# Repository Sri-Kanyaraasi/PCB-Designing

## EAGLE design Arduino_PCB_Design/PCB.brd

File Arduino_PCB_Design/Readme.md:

Eagle schematic file (with the extension .sch)  
Eagle board file (with the extension .brd)  
Geerber file  
PDF for PCB (Outlayer of the PCB)  
PNG of the GERBER file (Nothing but the PCB Picture)

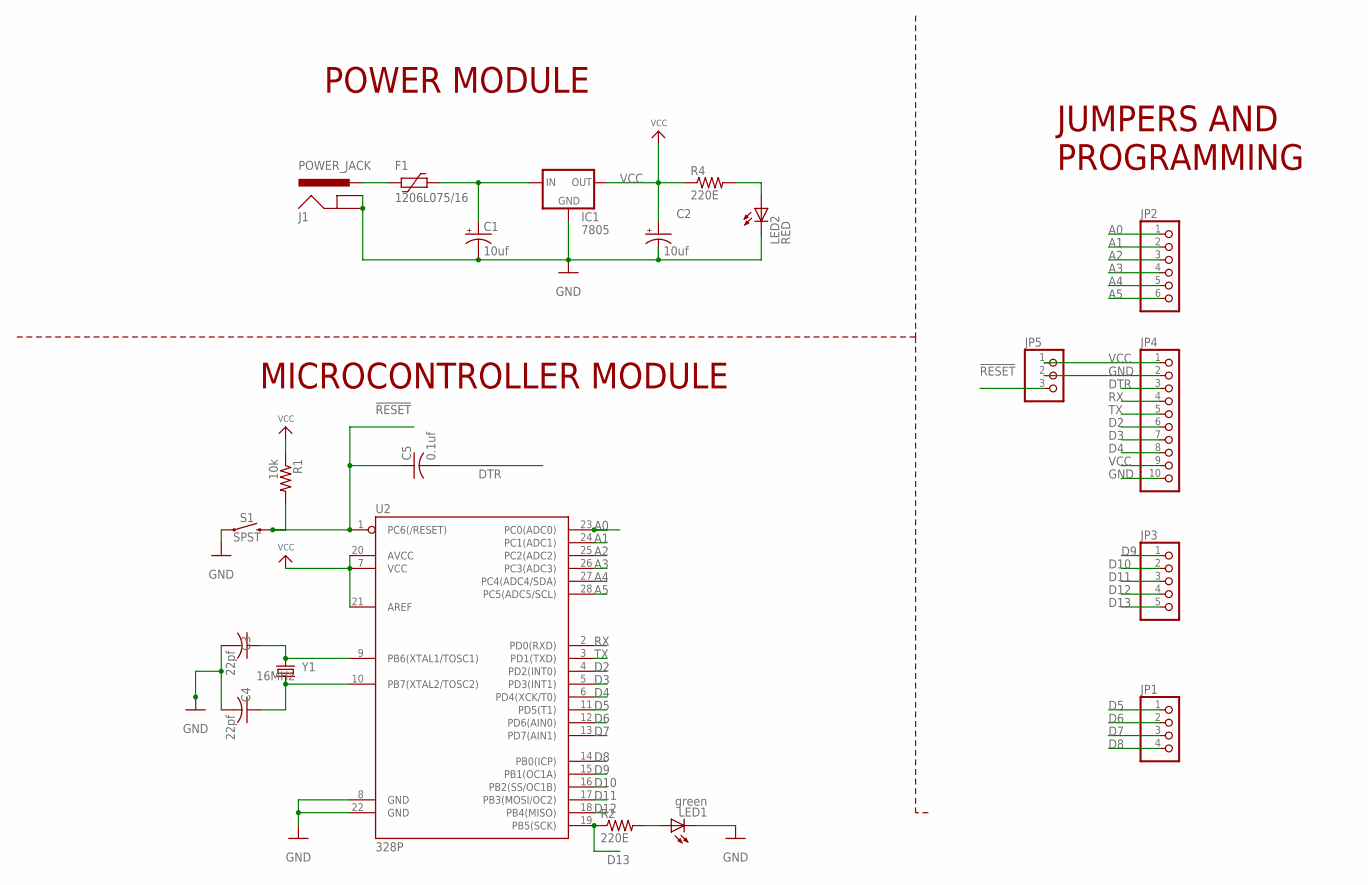
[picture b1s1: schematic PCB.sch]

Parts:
C1, C2: 10uf; E2,5-6
C3, C4: 22pf; C025-024X044
C5: 0.1uf; C025-024X044
F1: 1206L075/16; 1206L
IC1: 7805; 78XXS
J1: POWER_JACK; POWER_JACK_PTH
JP1: PINHD-1X4; 1X04
JP2: PINHD-1X6; 1X06
JP3: PINHD-1X5; 1X05
JP4: PINHD-1X10; 1X10
JP5: PINHD-1X3; 1X03
LED1: green; LED3MM
LED2: RED; LED3MM
R1: 10k; 0204/7
R2, R4: 220E; 0204/7
S1: SPST; TACTILE_SWITCH_PTH_6.0MM
U2: 328P; DIP28
Y1: 16MHz; HC49US

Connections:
!RESET: C5.1, JP5.3, R1.2, S1.3 (2), U2.1 (PC6(/RESET))
A0: JP2.1, U2.23 (PC0(ADC0))
A1: JP2.2, U2.24 (PC1(ADC1))
A2: JP2.3, U2.25 (PC2(ADC2))
A3: JP2.4, U2.26 (PC3(ADC3))
A4: JP2.5, U2.27 (PC4(ADC4/SDA))
A5: JP2.6, U2.28 (PC5(ADC5/SCL))
D2: JP4.6, U2.4 (PD2(INT0))
D3: JP4.7, U2.5 (PD3(INT1))
D4: JP4.8, U2.6 (PD4(XCK/T0))
D5: JP1.1, U2.11 (PD5(T1))
D6: JP1.2, U2.12 (PD6(AIN0))
D7: JP1.3, U2.13 (PD7(AIN1))
D8: JP1.4, U2.14 (PB0(ICP))
D9: JP3.1, U2.15 (PB1(OC1A))
D10: JP3.2, U2.16 (PB2(SS/OC1B))
D11: JP3.3, U2.17 (PB3(MOSI/OC2))
D12: JP3.4, U2.18 (PB4(MISO))
D13: JP3.5, R2.1, U2.19 (PB5(SCK))
DTR: C5.2, JP4.3
GND: C3.2, C4.2, JP4.2, JP4.10, JP5.2, LED1.K (C), S1.1, U2.8 (GND), U2.22 (GND)
unnamed: C1.+, F1.1, IC1.IN
unnamed: C3.1, U2.9 (PB6(XTAL1/TOSC1)), Y1.1
unnamed: C1.-, C2.-, IC1.GND, J1.GND, J1.GNDBREAK, LED2.K (C)
unnamed: C4.1, U2.10 (PB7(XTAL2/TOSC2)), Y1.2
unnamed: LED2.A, R4.2
unnamed: LED1.A, R2.2
unnamed: F1.2, J1.PWR
RX: JP4.4, U2.2 (PD0(RXD))
TX: JP4.5, U2.3 (PD1(TXD))
VCC: C2.+, IC1.OUT, JP4.1, JP4.9, JP5.1, R1.1, R4.1, U2.7 (VCC), U2.20 (AVCC), U2.21 (AREF)

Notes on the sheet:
POWER MODULE
MICROCONTROLLER MODULE
JUMPERS AND PROGRAMMING

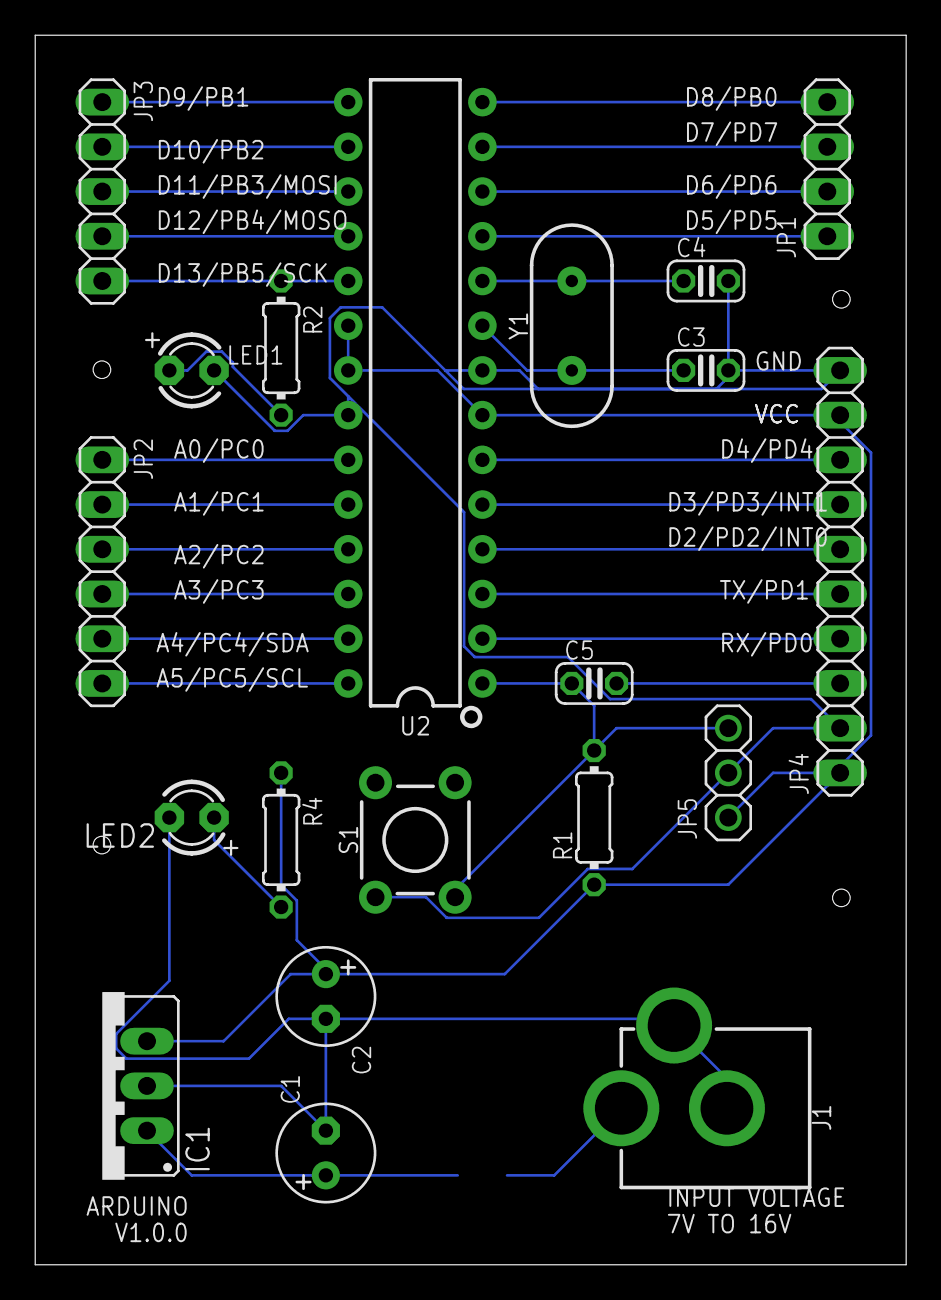
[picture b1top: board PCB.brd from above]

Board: 2 copper layers, 49.5 x 69.8 mm, 21 parts (1 on the bottom side), 31 nets.

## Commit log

2023-07-12 Create STM32_PCB
2023-07-13 Rename STM32_PCB to readme.md

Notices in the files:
parts and their libraries:
SparkFun-Connectors: Licensing: Creative Commons ShareAlike 4.0 International - https://creativecommons.org/licenses/by-sa/4.0
